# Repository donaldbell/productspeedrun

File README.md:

# Product Speedrun

**Product Speedrun** is a show about racing a randomly rolled product idea to a showcase-ready concept: an enclosure design, a circuit board and a product page. Everything the show designs is open, and this repository holds it.

**See the products:** https://donaldbell.github.io/productspeedrun/

Every product here is a **design proposal**, not something you can buy. Nothing has been manufactured, and each page lists what we still don't know.

## What's here

```
episodes/<NNN-slug>/        one folder per episode (Rev A, as aired)
  2-concept/, 3-layout/     concept art and control drawings
  4-model/                  the enclosure: model.step, model.stl, model.glb, notes
  5-electronics/            the circuit board: KiCad project, bom.csv, schematic and board renders, notes
  6-showcase/               the product page
products/<product>/rev-b/   later revisions of products we kept building, including firmware (7-firmware/)
tools/kicad/footprints/     custom footprints the KiCad projects use
tools/kicad/models/         3D models of parts the KiCad projects use
kit/                        the shared look of the product pages
```

## Using the designs

- **Enclosures:** open `4-model/model.step` in any CAD program, or print from `model.stl`. `build_model.py` and `model.solidcraft` are kept as a record of how the model was made; edit the STEP file.
- **Circuit boards:** open the `.kicad_pro` in [KiCad](https://www.kicad.org/) (the version each board was saved with is on its page). Keep the repository's folder layout so the custom footprints and 3D models in `tools/kicad/` are found. `src/design.py` and `src/layout.py` record the parts, nets and placement the board was generated from; edit the KiCad files.
- **Firmware:** PlatformIO projects in `products/<product>/rev-*/7-firmware/`.
- Each product page has a **Build on it** section with direct downloads and a prompt that hands the project to an AI coding agent.

## Licence and credit

Hardware is under CERN-OHL-P v2, writing and images under CC BY 4.0, and code under MIT. Details are in [LICENSE](LICENSE), the full texts in [LICENSES/](LICENSES/), and who made each episode in [CREDITS.md](CREDITS.md).

Credit line for reuse: *Based on Product Speedrun episode NNN by Donald Bell and &lt;guest&gt;, https://donaldbell.github.io/productspeedrun/*

The name "Product Speedrun" and its logo aren't covered by these licences.

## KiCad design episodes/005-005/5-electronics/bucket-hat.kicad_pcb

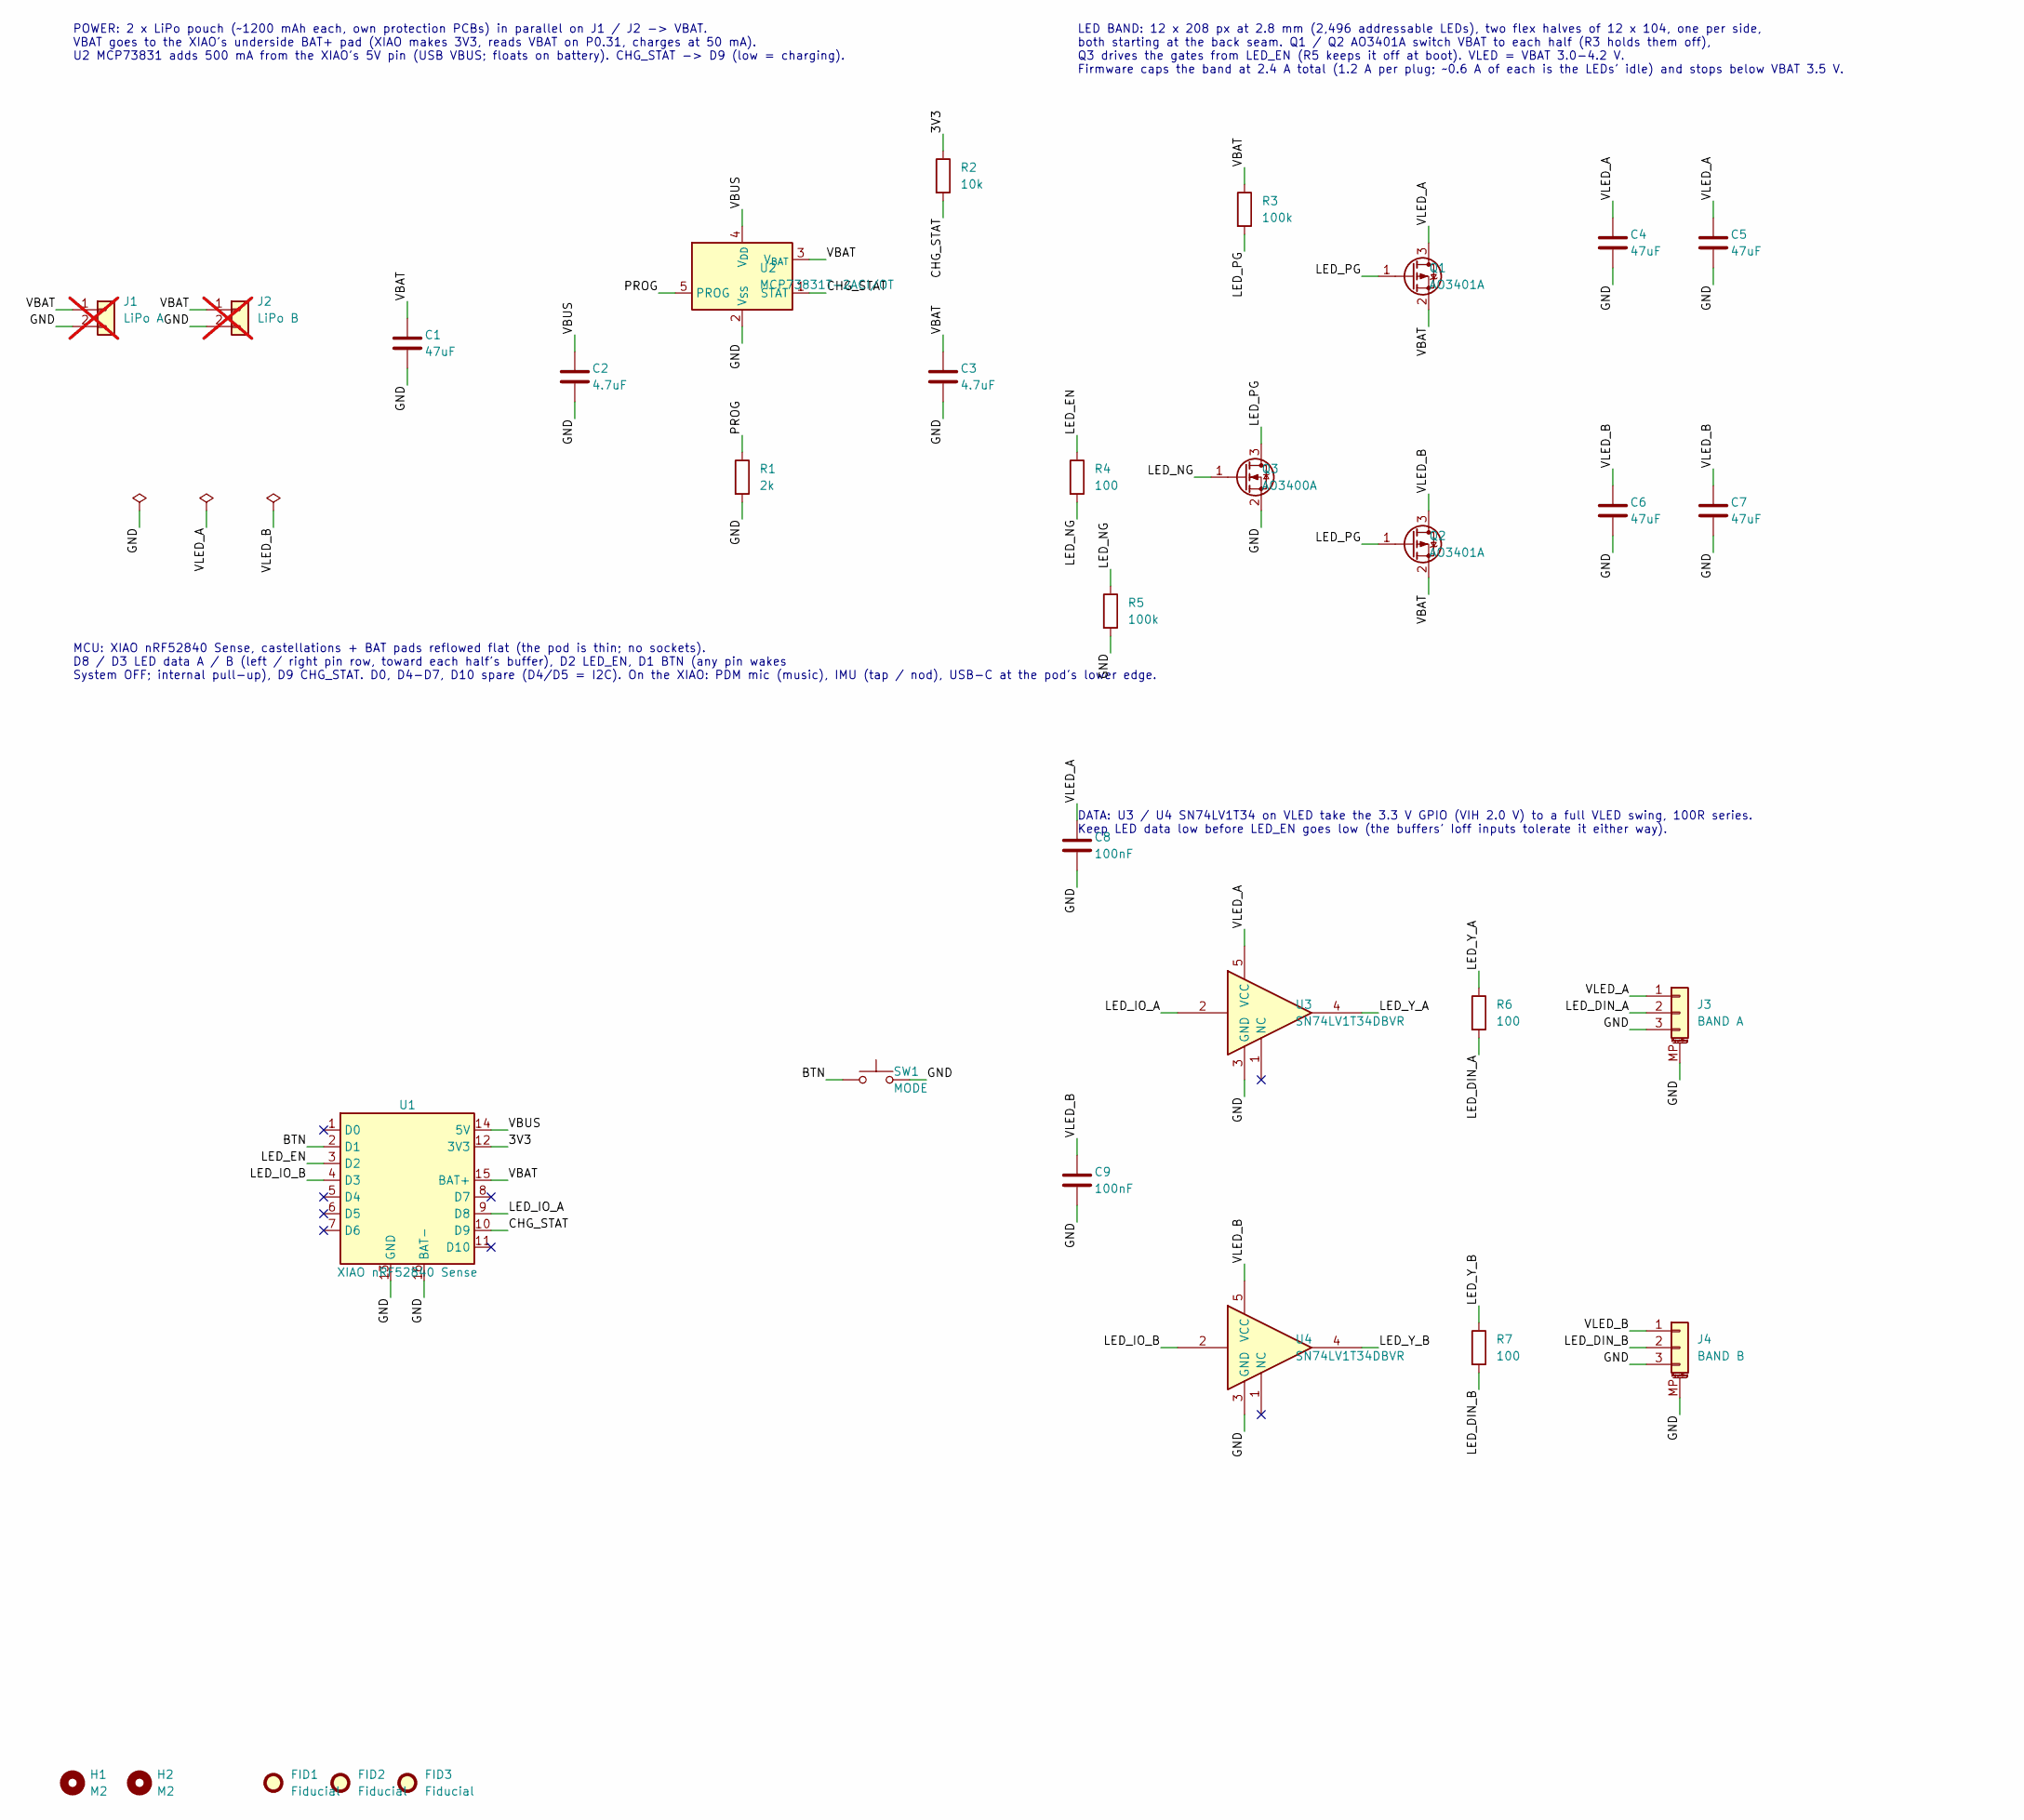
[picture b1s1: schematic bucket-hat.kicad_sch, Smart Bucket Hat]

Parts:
C1, C4, C5, C6, C7: 47uF; C_1206_3216Metric; MPN CL31A476MQHNNNE; LCSC C96123
C2, C3: 4.7uF; C_0603_1608Metric; MPN CL10A475KO8NNNC; LCSC C19666
C8, C9: 100nF; C_0603_1608Metric; MPN CC0603KRX7R9BB104; LCSC C14663
FID1, FID2, FID3: Fiducial; Fiducial_1mm_Mask2mm
H1, H2: M2; MountingHole_2.2mm_M2
J1: LiPo A; SolderWire-0.1sqmm_1x02_P3.6mm_D0.4mm_OD1mm; not fitted
J2: LiPo B; SolderWire-0.1sqmm_1x02_P3.6mm_D0.4mm_OD1mm; not fitted
J3: BAND A; JST_PH_S3B-PH-SM4-TB_1x03-1MP_P2.00mm_Horizontal; MPN S3B-PH-SM4-TB(LF)(SN)
J4: BAND B; JST_PH_S3B-PH-SM4-TB_1x03-1MP_P2.00mm_Horizontal; MPN S3B-PH-SM4-TB(LF)(SN)
Q1, Q2: AO3401A; SOT-23; MPN AO3401A; LCSC C15127
Q3: AO3400A; SOT-23; MPN AO3400A; LCSC C20917
R1: 2k; R_0603_1608Metric; MPN 0603WAF2001T5E; LCSC C22975
R2: 10k; R_0603_1608Metric; MPN 0603WAF1002T5E; LCSC C25804
R3, R5: 100k; R_0603_1608Metric; MPN 0603WAF1003T5E; LCSC C25803
R4, R6, R7: 100; R_0603_1608Metric; MPN 0603WAF1000T5E; LCSC C22775
SW1: MODE; SW_SPST_PTS810; MPN PTS810 SJM 250 SMTR LFS
U1: XIAO nRF52840 Sense; Seeed_XIAO_nRF52840_SMD; MPN 102010448
U2: MCP73831T-2ACI/OT; SOT-23-5; MPN MCP73831T-2ACI/OT; LCSC C424093
U3, U4: SN74LV1T34DBVR; SOT-23-5; MPN SN74LV1T34DBVR; LCSC C100024

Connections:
/3V3: R2.1, U1.12 (3V3)
/BTN: SW1.1, U1.2 (D1)
/CHG_STAT: R2.2, U1.10 (D9), U2.1 (STAT)
/GND: C1.2, C2.2, C3.2, C4.2, C5.2, C6.2, C7.2, C8.2, C9.2, J1.2, J2.2, J3.3, J3.MP (MountPin), J4.3, J4.MP (MountPin), Q3.2 (S), R1.2, R5.2, SW1.2, U1.13 (GND), U1.16 (BAT-), U2.2 (V_{SS}), U3.3 (GND), U4.3 (GND)
/LED_DIN_A: J3.2, R6.2
/LED_DIN_B: J4.2, R7.2
/LED_EN: R4.1, U1.3 (D2)
/LED_IO_A: U1.9 (D8), U3.2
/LED_IO_B: U1.4 (D3), U4.2
/LED_NG: Q3.1 (G), R4.2, R5.1
/LED_PG: Q1.1 (G), Q2.1 (G), Q3.3 (D), R3.2
/LED_Y_A: R6.1, U3.4
/LED_Y_B: R7.1, U4.4
/PROG: R1.1, U2.5 (PROG)
/VBAT: C1.1, C3.1, J1.1, J2.1, Q1.2 (S), Q2.2 (S), R3.1, U1.15 (BAT+), U2.3 (V_{BAT})
/VBUS: C2.1, U1.14 (5V), U2.4 (V_{DD})
/VLED_A: C4.1, C5.1, C8.1, J3.1, Q1.3 (D), U3.5 (VCC)
/VLED_B: C6.1, C7.1, C9.1, J4.1, Q2.3 (D), U4.5 (VCC)

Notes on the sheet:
POWER: 2 x LiPo pouch (~1200 mAh each, own protection PCBs) in parallel on J1 / J2 -> VBAT. VBAT goes to the XIAO's underside BAT+ pad (XIAO makes 3V3, reads VBAT on P0.31, charges at 50 mA). U2 MCP73831 adds 500 mA from the XIAO's 5V pin (USB VBUS; floats on battery). CHG_STAT -> D9 (low = chargin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
MCU: XIAO nRF52840 Sense, castellations + BAT pads reflowed flat (the pod is thin; no sockets). D8 / D3 LED data A / B (left / right pin row, toward each half's buffer), D2 LED_EN, D1 BTN (any pin wakes System OFF; internal pull-up), D9 CHG_STAT. D0, D4-D7, D10 spare (D4/D5 = I2C). On the XIAO: PDM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
LED BAND: 12 x 208 px at 2.8 mm (2,496 addressable LEDs), two flex halves of 12 x 104, one per side, both starting at the back seam. Q1 / Q2 AO3401A switch VBAT to each half (R3 holds them off), Q3 drives the gates from LED_EN (R5 keeps it off at boot). VLED = VBAT 3.0-4.2 V. Firmware caps the band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
DATA: U3 / U4 SN74LV1T34 on VLED take the 3.3 V GPIO (VIH 2.0 V) to a full VLED swing, 100R series. Keep LED data low before LED_EN goes low (the buffers' Ioff inputs tolerate it either way).

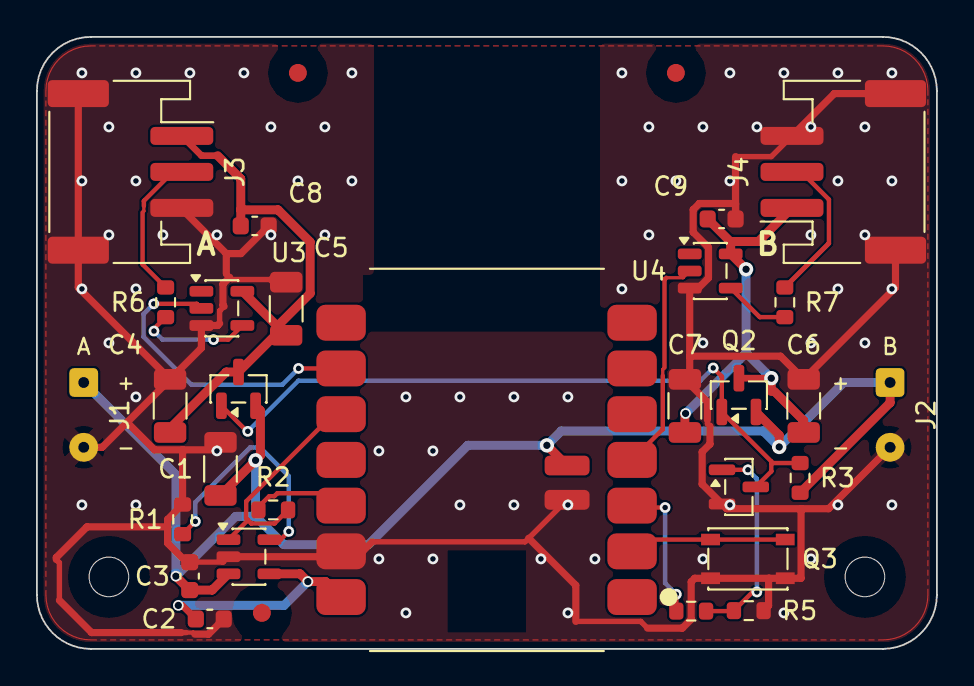
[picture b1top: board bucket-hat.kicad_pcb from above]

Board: 2 copper layers, 50.0 x 34.0 mm, 33 parts (0 on the bottom side), 18 nets.

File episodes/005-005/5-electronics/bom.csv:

Ref,Qty,Value,Description,Footprint,MPN
C1 C4 C5 C6 C7,5,47uF,"Capacitor, ceramic, 47 uF 6.3 V X5R 1206 (bulk on a battery rail)",C_1206_3216Metric,CL31A476MQHNNNE
C2 C3,2,4.7uF,"Capacitor, ceramic, 4.7 uF 16 V X5R 0603",C_0603_1608Metric,CL10A475KO8NNNC
C8 C9,2,100nF,"Capacitor, ceramic, 100 nF 50 V X7R 0603",C_0603_1608Metric,CC0603KRX7R9BB104
J3,1,BAND A,"JST PH 3-pin SMD side entry: LED band half A (VLED, DIN, GND); the pod unplugs for washing",JST_PH_S3B-PH-SM4-TB_1x03-1MP_P2.00mm_Horizontal,S3B-PH-SM4-TB(LF)(SN)
J4,1,BAND B,"JST PH 3-pin SMD side entry: LED band half B (VLED, DIN, GND); the pod unplugs for washing",JST_PH_S3B-PH-SM4-TB_1x03-1MP_P2.00mm_Horizontal,S3B-PH-SM4-TB(LF)(SN)
Q1 Q2,2,AO3401A,"P-MOSFET -30 V -4 A SOT-23: high-side switch, band half A",SOT-23,AO3401A
Q3,1,AO3400A,N-MOSFET 30 V 5.7 A SOT-23: drives Q1/Q2's gates from the 3.3 V GPIO,SOT-23,AO3400A
R1,1,2k,"Resistor, 1 %, 0603, 2k",R_0603_1608Metric,0603WAF2001T5E
R2,1,10k,"Resistor, 1 %, 0603, 10k",R_0603_1608Metric,0603WAF1002T5E
R3 R5,2,100k,"Resistor, 1 %, 0603, 100k",R_0603_1608Metric,0603WAF1003T5E
R4 R6 R7,3,100,"Resistor, 1 %, 0603, 100",R_0603_1608Metric,0603WAF1000T5E
SW1,1,MODE,"Tact switch 4.2 x 3.2 x 2.5 mm SMD, pressed through the pod's inner face: wake, next show, hold = beacon / off",SW_SPST_PTS810,PTS810 SJM 250 SMTR LFS
U1,1,XIAO nRF52840 Sense,"Seeed XIAO nRF52840 Sense (BLE 5, USB-C, LiPo charger, 3.3 V LDO, PDM mic, IMU), castellations + BAT pads reflowed to the carrier",Seeed_XIAO_nRF52840_SMD,102010448
U2,1,MCP73831T-2ACI/OT,"Li-ion/LiPo linear charger 4.2 V, 500 mA (R1 2k), SOT-23-5: fills the pack ~5x faster than the XIAO's own",SOT-23-5,MCP73831T-2ACI/OT
U3 U4,2,SN74LV1T34DBVR,"Single buffer with 3.3 V-compatible inputs, powered from VLED: full-swing data for band half A",SOT-23-5,SN74LV1T34DBVR
BT1,1,LiPo ~1200 mAh,"LiPo pouch 3.7 V ~1200 mAh, ~6 x 34 x 50 mm (603450), with protection PCB, leads soldered to J1",off-board,generic 603450
BT2,1,LiPo ~1200 mAh,"Second, matching cell in parallel, leads soldered to J2 (charge both to the same voltage before joining)",off-board,generic 603450
LB1,1,LED band half A,"Flex matrix 12 x 104 addressable RGB LEDs (1515 / 1010 size, 2.8 mm pitch, ~34 x 292 mm), JST PH 3-pin lead (VLED, DIN, GND)",off-board,custom flex
LB2,1,LED band half B,"Second band half, mirrored, same JST PH 3-pin lead",off-board,custom flex

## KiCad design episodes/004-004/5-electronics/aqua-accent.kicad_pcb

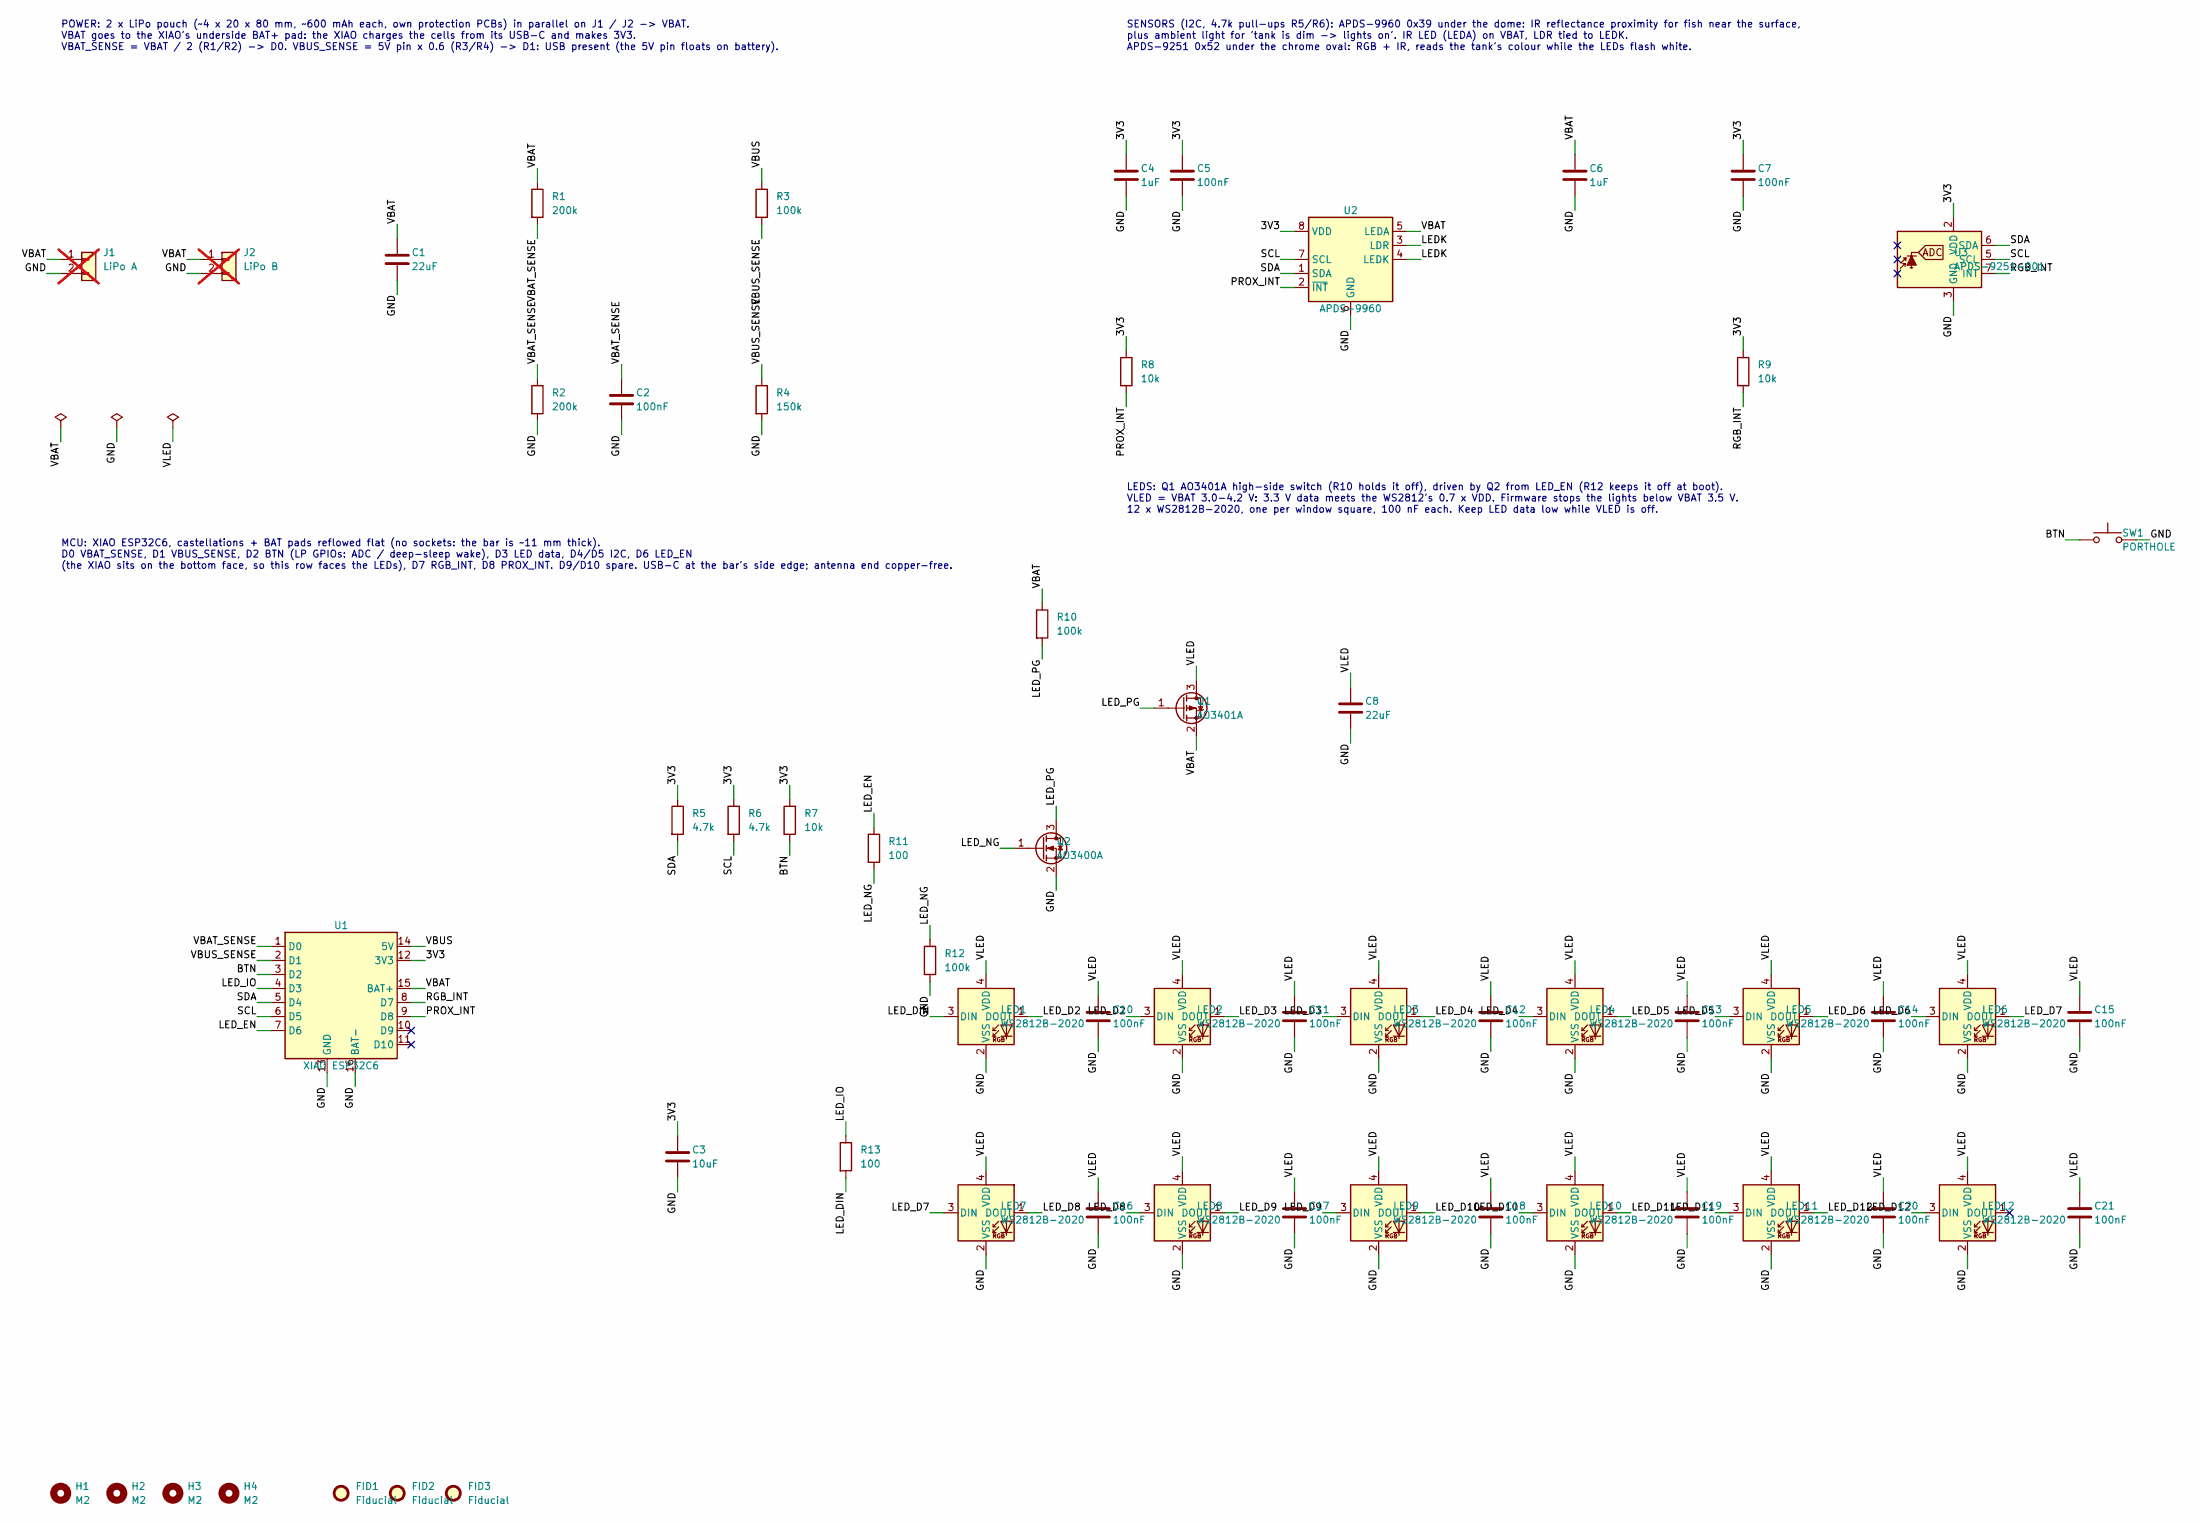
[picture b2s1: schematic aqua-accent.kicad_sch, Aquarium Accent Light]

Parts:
C1, C8: 22uF; C_0805_2012Metric; MPN CL21A226MAQNNNE; LCSC C45783
C2, C5, C7, C10, C11, C12, C13, C14, C15, C16, C17, C18, C19, C20, C21: 100nF; C_0603_1608Metric; MPN CC0603KRX7R9BB104; LCSC C14663
C3: 10uF; C_0805_2012Metric; MPN CL21A106KAYNNNE; LCSC C15850
C4, C6: 1uF; C_0603_1608Metric; MPN CL10A105KB8NNNC; LCSC C15849
FID1, FID2, FID3: Fiducial; Fiducial_1mm_Mask2mm
H1, H2, H3, H4: M2; MountingHole_2.2mm_M2
J1: LiPo A; SolderWire-0.1sqmm_1x02_P3.6mm_D0.4mm_OD1mm; not fitted
J2: LiPo B; SolderWire-0.1sqmm_1x02_P3.6mm_D0.4mm_OD1mm; not fitted
LED1, LED2, LED3, LED4, LED5, LED6, LED7, LED8, LED9, LED10, LED11, LED12: WS2812B-2020; LED_WS2812B-2020_PLCC4_2.0x2.0mm; MPN WS2812B-2020; LCSC C965555
Q1: AO3401A; SOT-23; MPN AO3401A; LCSC C15127
Q2: AO3400A; SOT-23; MPN AO3400A; LCSC C20917
R1, R2: 200k; R_0603_1608Metric; MPN 0603WAF2003T5E; LCSC C25811
R3, R10, R12: 100k; R_0603_1608Metric; MPN 0603WAF1003T5E; LCSC C25803
R4: 150k; R_0603_1608Metric; MPN 0603WAF1503T5E; LCSC C22807
R5, R6: 4.7k; R_0603_1608Metric; MPN 0603WAF4701T5E; LCSC C23162
R7, R8, R9: 10k; R_0603_1608Metric; MPN 0603WAF1002T5E; LCSC C25804
R11, R13: 100; R_0603_1608Metric; MPN 0603WAF1000T5E; LCSC C22775
SW1: PORTHOLE; SW_SPST_PTS810; MPN PTS810 SJM 250 SMTR LFS
U1: XIAO ESP32C6; Seeed_XIAO_ESP32C6_SMD; MPN 113991254
U2: APDS-9960; Avago_APDS-9960; MPN APDS-9960
U3: APDS-9251-001; Broadcom_LGA-8_2x2mm_P0.5mm; MPN APDS-9251-001

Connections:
/3V3: C3.1, C4.1, C5.1, C7.1, R5.1, R6.1, R7.1, R8.1, R9.1, U1.12 (3V3), U2.8 (VDD), U3.2 (VDD)
/BTN: R7.2, SW1.1, U1.3 (D2)
/GND: C1.2, C2.2, C3.2, C4.2, C5.2, C6.2, C7.2, C8.2, C10.2, C11.2, C12.2, C13.2, C14.2, C15.2, C16.2, C17.2, C18.2, C19.2, C20.2, C21.2, J1.2, J2.2, LED1.2 (VSS), LED2.2 (VSS), LED3.2 (VSS), LED4.2 (VSS), LED5.2 (VSS), LED6.2 (VSS), LED7.2 (VSS), LED8.2 (VSS), LED9.2 (VSS), LED10.2 (VSS), LED11.2 (VSS), LED12.2 (VSS), Q2.2 (S), R2.2, R4.2, R12.2, SW1.2, U1.13 (GND), U1.16 (BAT-), U2.6 (GND), U3.3 (GND)
/LEDK: U2.3 (LDR), U2.4 (LEDK)
/LED_D2: LED1.1 (DOUT), LED2.3 (DIN)
/LED_D3: LED2.1 (DOUT), LED3.3 (DIN)
/LED_D4: LED3.1 (DOUT), LED4.3 (DIN)
/LED_D5: LED4.1 (DOUT), LED5.3 (DIN)
/LED_D6: LED5.1 (DOUT), LED6.3 (DIN)
/LED_D7: LED6.1 (DOUT), LED7.3 (DIN)
/LED_D8: LED7.1 (DOUT), LED8.3 (DIN)
/LED_D9: LED8.1 (DOUT), LED9.3 (DIN)
/LED_D10: LED9.1 (DOUT), LED10.3 (DIN)
/LED_D11: LED10.1 (DOUT), LED11.3 (DIN)
/LED_D12: LED11.1 (DOUT), LED12.3 (DIN)
/LED_DIN: LED1.3 (DIN), R13.2
/LED_EN: R11.1, U1.7 (D6)
/LED_IO: R13.1, U1.4 (D3)
/LED_NG: Q2.1 (G), R11.2, R12.1
/LED_PG: Q1.1 (G), Q2.3 (D), R10.2
/PROX_INT: R8.2, U1.9 (D8), U2.2 (~INT)
/RGB_INT: R9.2, U1.8 (D7), U3.7 (INT)
/SCL: R6.2, U1.6 (D5), U2.7 (SCL), U3.5 (SCL)
/SDA: R5.2, U1.5 (D4), U2.1 (SDA), U3.6 (SDA)
/VBAT: C1.1, C6.1, J1.1, J2.1, Q1.2 (S), R1.1, R10.1, U1.15 (BAT+), U2.5 (LEDA)
/VBAT_SENSE: C2.1, R1.2, R2.1, U1.1 (D0)
/VBUS: R3.1, U1.14 (5V)
/VBUS_SENSE: R3.2, R4.1, U1.2 (D1)
/VLED: C8.1, C10.1, C11.1, C12.1, C13.1, C14.1, C15.1, C16.1, C17.1, C18.1, C19.1, C20.1, C21.1, LED1.4 (VDD), LED2.4 (VDD), LED3.4 (VDD), LED4.4 (VDD), LED5.4 (VDD), LED6.4 (VDD), LED7.4 (VDD), LED8.4 (VDD), LED9.4 (VDD), LED10.4 (VDD), LED11.4 (VDD), LED12.4 (VDD), Q1.3 (D)

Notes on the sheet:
POWER: 2 x LiPo pouch (~4 x 20 x 80 mm, ~600 mAh each, own protection PCBs) in parallel on J1 / J2 -> VBAT. VBAT goes to the XIAO's underside BAT+ pad: the XIAO charges the cells from its USB-C and makes 3V3. VBAT_SENSE = VBAT / 2 (R1/R2) -> D0. VBUS_SENSE = 5V pin x 0.6 (R3/R4) -> D1: USB present 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
MCU: XIAO ESP32C6, castellations + BAT pads reflowed flat (no sockets: the bar is ~11 mm thick). D0 VBAT_SENSE, D1 VBUS_SENSE, D2 BTN (LP GPIOs: ADC / deep-sleep wake), D3 LED data, D4/D5 I2C, D6 LED_EN (the XIAO sits on the bottom face, so this row faces the LEDs), D7 RGB_INT, D8 PROX_INT. D9/D10 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
SENSORS (I2C, 4.7k pull-ups R5/R6): APDS-9960 0x39 under the dome: IR reflectance proximity for fish near the surface, plus ambient light for 'tank is dim -> lights on'. IR LED (LEDA) on VBAT, LDR tied to LEDK. APDS-9251 0x52 under the chrome oval: RGB + IR, reads the tank's colour while the LEDs f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
LEDS: Q1 AO3401A high-side switch (R10 holds it off), driven by Q2 from LED_EN (R12 keeps it off at boot). VLED = VBAT 3.0-4.2 V: 3.3 V data meets the WS2812's 0.7 x VDD. Firmware stops the lights below VBAT 3.5 V. 12 x WS2812B-2020, one per window square, 100 nF each. Keep LED data low while VLED 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

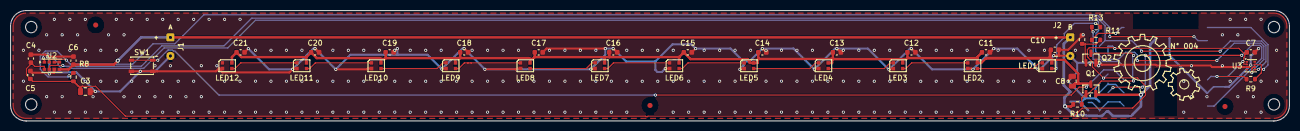
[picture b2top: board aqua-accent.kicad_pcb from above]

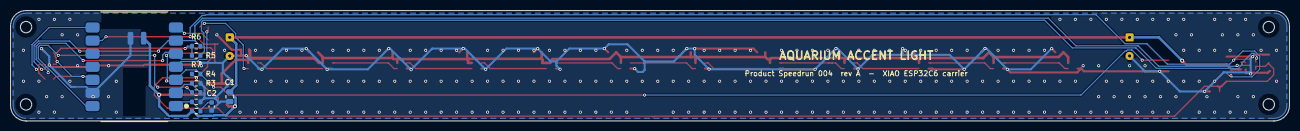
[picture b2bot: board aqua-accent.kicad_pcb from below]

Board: 2 copper layers, 248.0 x 21.4 mm, 60 parts (10 on the bottom side), 29 nets.

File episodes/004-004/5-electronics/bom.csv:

Ref,Qty,Value,Description,Footprint,MPN
C1 C8,2,22uF,"Capacitor, ceramic, 22 uF 25 V X5R 0805",C_0805_2012Metric,CL21A226MAQNNNE
C2 C5 C7 C10 C11 C12 C13 C14 C15 C16 C17 C18 C19 C20 C21,15,100nF,"Capacitor, ceramic, 100 nF 50 V X7R 0603",C_0603_1608Metric,CC0603KRX7R9BB104
C3,1,10uF,"Capacitor, ceramic, 10 uF 25 V X5R 0805",C_0805_2012Metric,CL21A106KAYNNNE
C4 C6,2,1uF,"Capacitor, ceramic, 1 uF 50 V X5R 0603",C_0603_1608Metric,CL10A105KB8NNNC
LED1 LED2 LED3 LED4 LED5 LED6 LED7 LED8 LED9 LED10 LED11 LED12,12,WS2812B-2020,"RGB LED 2 x 2 mm, one under each of the 12 window squares",LED_WS2812B-2020_PLCC4_2.0x2.0mm,WS2812B-2020
Q1,1,AO3401A,P-MOSFET -30 V -4 A SOT-23: high-side switch for the LED chain,SOT-23,AO3401A
Q2,1,AO3400A,N-MOSFET 30 V 5.7 A SOT-23: drives Q1's gate from the 3.3 V GPIO,SOT-23,AO3400A
R1 R2,2,200k,"Resistor, 1 %, 0603, 200k",R_0603_1608Metric,0603WAF2003T5E
R3 R10 R12,3,100k,"Resistor, 1 %, 0603, 100k",R_0603_1608Metric,0603WAF1003T5E
R4,1,150k,"Resistor, 1 %, 0603, 150k",R_0603_1608Metric,0603WAF1503T5E
R5 R6,2,4.7k,"Resistor, 1 %, 0603, 4.7k",R_0603_1608Metric,0603WAF4701T5E
R7 R8 R9,3,10k,"Resistor, 1 %, 0603, 10k",R_0603_1608Metric,0603WAF1002T5E
R11 R13,2,100,"Resistor, 1 %, 0603, 100",R_0603_1608Metric,0603WAF1000T5E
SW1,1,PORTHOLE,"Tact switch 4.2 x 3.2 x 2.5 mm SMD under the porthole boss: wake, mode, hold = open the control panel",SW_SPST_PTS810,PTS810 SJM 250 SMTR LFS
U1,1,XIAO ESP32C6,"Seeed XIAO ESP32C6 (USB-C, LiPo charger, 3.3 V LDO, ceramic antenna), castellations + BAT pads reflowed to the carrier",Seeed_XIAO_ESP32C6_SMD,113991254
U2,1,APDS-9960,"Proximity / gesture / ambient / RGBC sensor with IR LED, I2C 0x39: fish near the surface, room light",Avago_APDS-9960,APDS-9960
U3,1,APDS-9251-001,"Digital RGB + IR light sensor, I2C 0x52: reads the tank's colour",Broadcom_LGA-8_2x2mm_P0.5mm,APDS-9251-001
BT1,1,LiPo ~600 mAh,"LiPo pouch 3.7 V ~600 mAh, ~4 x 20 x 80 mm, with protection PCB, leads soldered to J1",off-board,generic 402080
BT2,1,LiPo ~600 mAh,"Second, matching cell in parallel, leads soldered to J2 (charge both to the same voltage before joining)",off-board,generic 402080

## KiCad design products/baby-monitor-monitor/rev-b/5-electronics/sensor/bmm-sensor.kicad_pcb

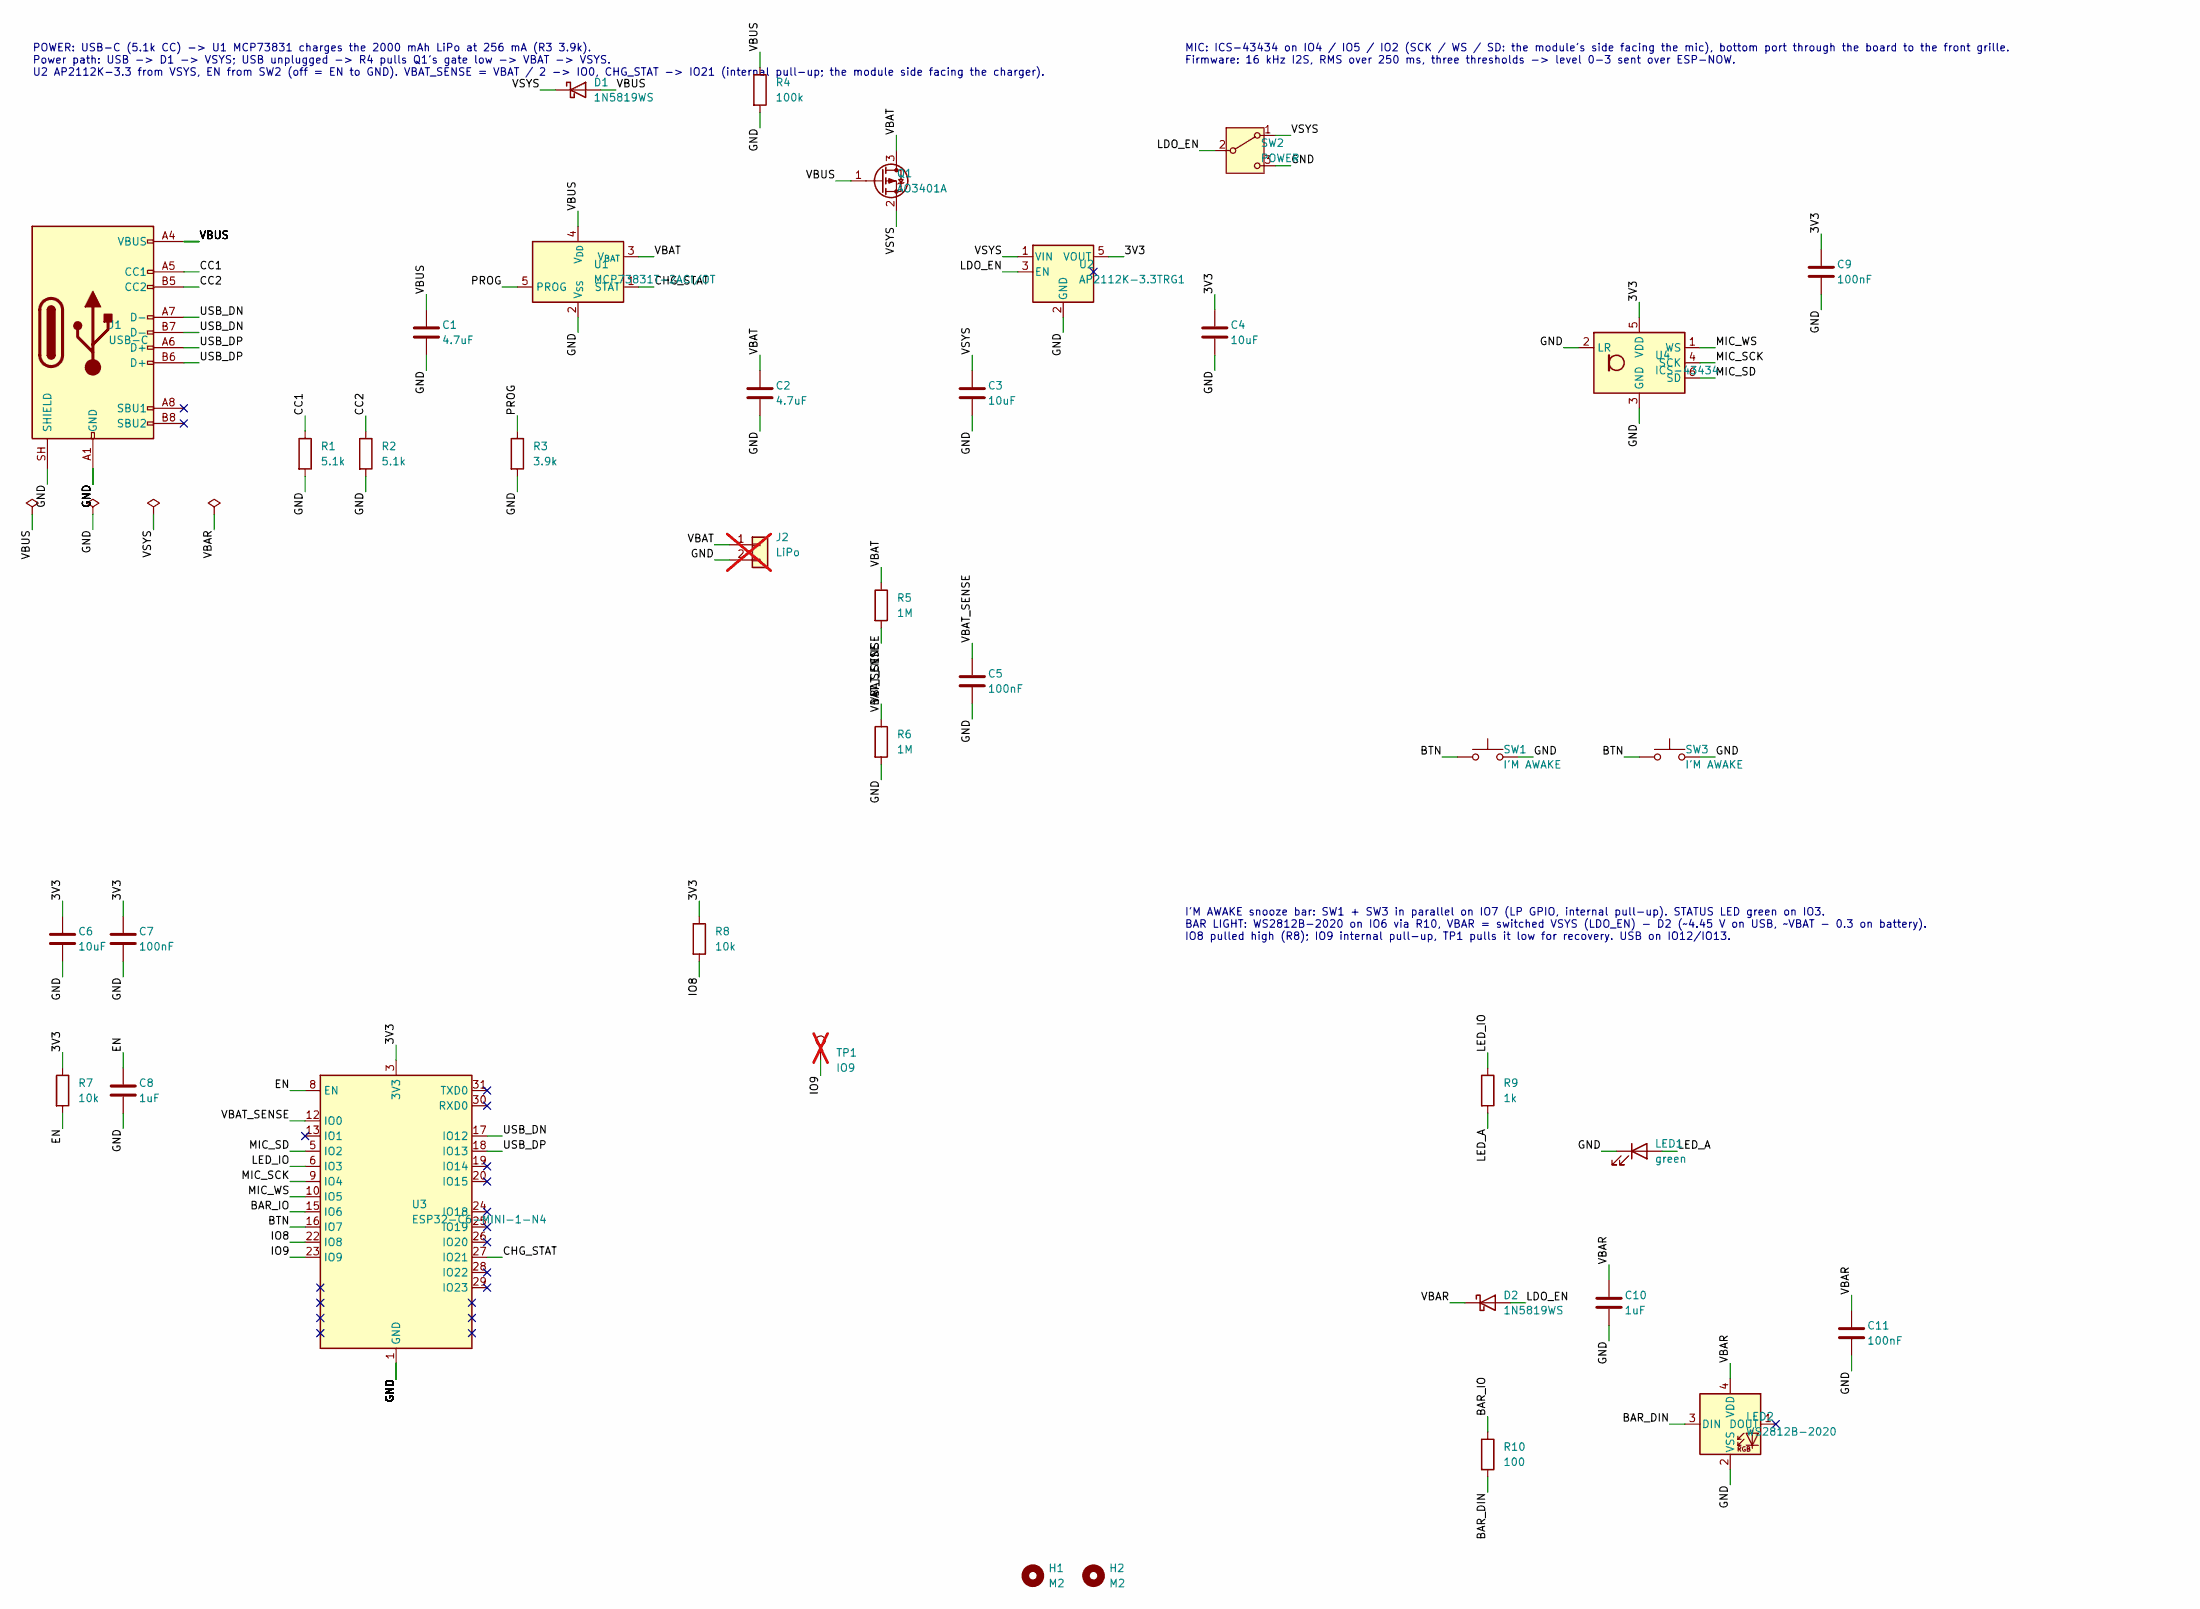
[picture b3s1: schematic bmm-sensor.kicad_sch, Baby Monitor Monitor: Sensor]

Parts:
C1, C2: 4.7uF; C_0603_1608Metric; MPN CL10A475KO8NNNC; LCSC C19666
C3, C4, C6: 10uF; C_0805_2012Metric; MPN CL21A106KAYNNNE; LCSC C15850
C5, C7, C9, C11: 100nF; C_0603_1608Metric; MPN CC0603KRX7R9BB104; LCSC C14663
C8, C10: 1uF; C_0603_1608Metric; MPN CL10A105KB8NNNC; LCSC C15849
D1, D2: 1N5819WS; D_SOD-323; MPN 1N5819WS; LCSC C191023
H1, H2: M2; MountingHole_2.2mm_M2
J1: USB-C; USB_C_Receptacle_GCT_USB4105-xx-A_16P_TopMnt_Horizontal; MPN USB4105-GF-A
J2: LiPo; SolderWire-0.1sqmm_1x02_P3.6mm_D0.4mm_OD1mm; not fitted
LED1: green; LED_0603_1608Metric; MPN KT-0603G; LCSC C72043
LED2: WS2812B-2020; LED_WS2812B-2020_PLCC4_2.0x2.0mm; MPN WS2812B-2020; LCSC C965555
Q1: AO3401A; SOT-23; MPN AO3401A; LCSC C15127
R1, R2: 5.1k; R_0603_1608Metric; MPN 0603WAF5101T5E; LCSC C23186
R3: 3.9k; R_0603_1608Metric; MPN 0603WAF3901T5E; LCSC C23018
R4: 100k; R_0603_1608Metric; MPN 0603WAF1003T5E; LCSC C25803
R5, R6: 1M; R_0603_1608Metric; MPN 0603WAF1004T5E; LCSC C22935
R7, R8: 10k; R_0603_1608Metric; MPN 0603WAF1002T5E; LCSC C25804
R9: 1k; R_0603_1608Metric; MPN 0603WAF1001T5E; LCSC C21190
R10: 100; R_0603_1608Metric; MPN 0603WAF1000T5E; LCSC C22775
SW1, SW3: I'M AWAKE; SW_Push_1TS009xxxx-xxxx-xxxx_6x6x5mm; MPN 1TS009A-1800-5000-CT
SW2: POWER; SW_SPDT_PCM12; MPN PCM12SMTR
TP1: IO9; TestPoint_Pad_D1.0mm; not fitted
U1: MCP73831T-2ACI/OT; SOT-23-5; MPN MCP73831T-2ACI/OT; LCSC C424093
U2: AP2112K-3.3TRG1; SOT-23-5; MPN AP2112K-3.3TRG1; LCSC C51118
U3: ESP32-C6-MINI-1-N4; ESP32-C6-MINI-1; MPN ESP32-C6-MINI-1-N4
U4: ICS-43434; InvenSense_ICS-43434-6_3.5x2.65mm; MPN ICS-43434

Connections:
/3V3: C4.1, C6.1, C7.1, C9.1, R7.1, R8.1, U2.5 (VOUT), U3.3 (3V3), U4.5 (VDD)
/BAR_DIN: LED2.3 (DIN), R10.2
/BAR_IO: R10.1, U3.15 (IO6)
/BTN: SW1.1, SW3.1, U3.16 (IO7)
/CC1: J1.A5 (CC1), R1.1
/CC2: J1.B5 (CC2), R2.1
/CHG_STAT: U1.1 (STAT), U3.27 (IO21)
/EN: C8.1, R7.2, U3.8 (EN)
/GND: C1.2, C2.2, C3.2, C4.2, C5.2, C6.2, C7.2, C8.2, C9.2, C10.2, C11.2, J1.A1 (GND), J1.A12 (GND), J1.B1 (GND), J1.B12 (GND), J1.SH (SHIELD), J2.2, LED1.1 (K), LED2.2 (VSS), R1.2, R2.2, R3.2, R4.2, R6.2, SW1.2, SW2.3 (C), SW3.2, U1.2 (V_{SS}), U2.2 (GND), U3.1 (GND), U3.2 (GND), U3.11 (GND), U3.14 (GND), U3.36 (GND), U3.37 (GND), U3.38 (GND), U3.39 (GND), U3.40 (GND), U3.41 (GND), U3.42 (GND), U3.43 (GND), U3.44 (GND), U3.45 (GND), U3.46 (GND), U3.47 (GND), U3.48 (GND), U3.49 (GND), U3.50 (GND), U3.51 (GND), U3.52 (GND), U3.53 (GND), U4.2 (LR), U4.3 (GND)
/IO8: R8.2, U3.22 (IO8)
/IO9: TP1.1, U3.23 (IO9)
/LDO_EN: D2.2 (A), SW2.2 (B), U2.3 (EN)
/LED_A: LED1.2 (A), R9.2
/LED_IO: R9.1, U3.6 (IO3)
/MIC_SCK: U3.9 (IO4), U4.4 (SCK)
/MIC_SD: U3.5 (IO2), U4.6 (SD)
/MIC_WS: U3.10 (IO5), U4.1 (WS)
/PROG: R3.1, U1.5 (PROG)
/USB_DN: J1.A7 (D-), J1.B7 (D-), U3.17 (IO12)
/USB_DP: J1.A6 (D+), J1.B6 (D+), U3.18 (IO13)
/VBAR: C10.1, C11.1, D2.1 (K), LED2.4 (VDD)
/VBAT: C2.1, J2.1, Q1.3 (D), R5.1, U1.3 (V_{BAT})
/VBAT_SENSE: C5.1, R5.2, R6.1, U3.12 (IO0)
/VBUS: C1.1, D1.2 (A), J1.A4 (VBUS), J1.A9 (VBUS), J1.B4 (VBUS), J1.B9 (VBUS), Q1.1 (G), R4.1, U1.4 (V_{DD})
/VSYS: C3.1, D1.1 (K), Q1.2 (S), SW2.1 (A), U2.1 (VIN)

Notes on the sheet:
POWER: USB-C (5.1k CC) -> U1 MCP73831 charges the 2000 mAh LiPo at 256 mA (R3 3.9k). Power path: USB -> D1 -> VSYS; USB unplugged -> R4 pulls Q1's gate low -> VBAT -> VSYS. U2 AP2112K-3.3 from VSYS, EN from SW2 (off = EN to GND). VBAT_SENSE = VBAT / 2 -> IO0, CHG_STAT -> IO21 (internal pull-up; the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
MIC: ICS-43434 on IO4 / IO5 / IO2 (SCK / WS / SD: the module's side facing the mic), bottom port through the board to the front grille. Firmware: 16 kHz I2S, RMS over 250 ms, three thresholds -> level 0-3 sent over ESP-NOW.
I'M AWAKE snooze bar: SW1 + SW3 in parallel on IO7 (LP GPIO, internal pull-up). STATUS LED green on IO3. BAR LIGHT: WS2812B-2020 on IO6 via R10, VBAR = switched VSYS (LDO_EN) - D2 (~4.45 V on USB, ~VBAT - 0.3 on battery). IO8 pulled high (R8); IO9 internal pull-up, TP1 pulls it low for recovery. US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
